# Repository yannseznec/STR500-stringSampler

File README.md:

## STR-500

This is all of the code and build info for the STR-500 gestural granular synthesizer. Watch this video for some background on the project and to see the instrument in action: https://youtu.be/luxsUPbPhyk 

The STR-500 is a granular synthesizer built for the Daisy Seed which uses a salvaged Gametrak string controller to playback a recorded sample. [Watch this video](https://youtu.be/GELGBzM0ZOE) for information on how to hack the strings out of a Gametrak. 

Here you will find a Pure Data system for running on the Daisy Seed, a KiCad project with the schematic and PCB design for the instrument, and a folder of information about the physical build including drill outlines and laser cutting files for the enclosure. Current working version is called v1.2. 

The project website can be found [here](https://www.impracticaldevices.com/docs/devices/str500/).

You can purchase a fully built STR-500, an STR-500 DIY kit, or a bare STR-500 PCB on the [Impractical Devices store on Lectronz](https://lectronz.com/stores/impracticaldevices). If they are sold out you can join the waitlist there to be notified when things are back in stock.

This project is produced by [Impractical Devices](https://www.impracticaldevices.com/), which is mainly the work of [Yann Seznec](http://www.yannseznec.com). Get in touch if you have any questions: yann@yannseznec.com.

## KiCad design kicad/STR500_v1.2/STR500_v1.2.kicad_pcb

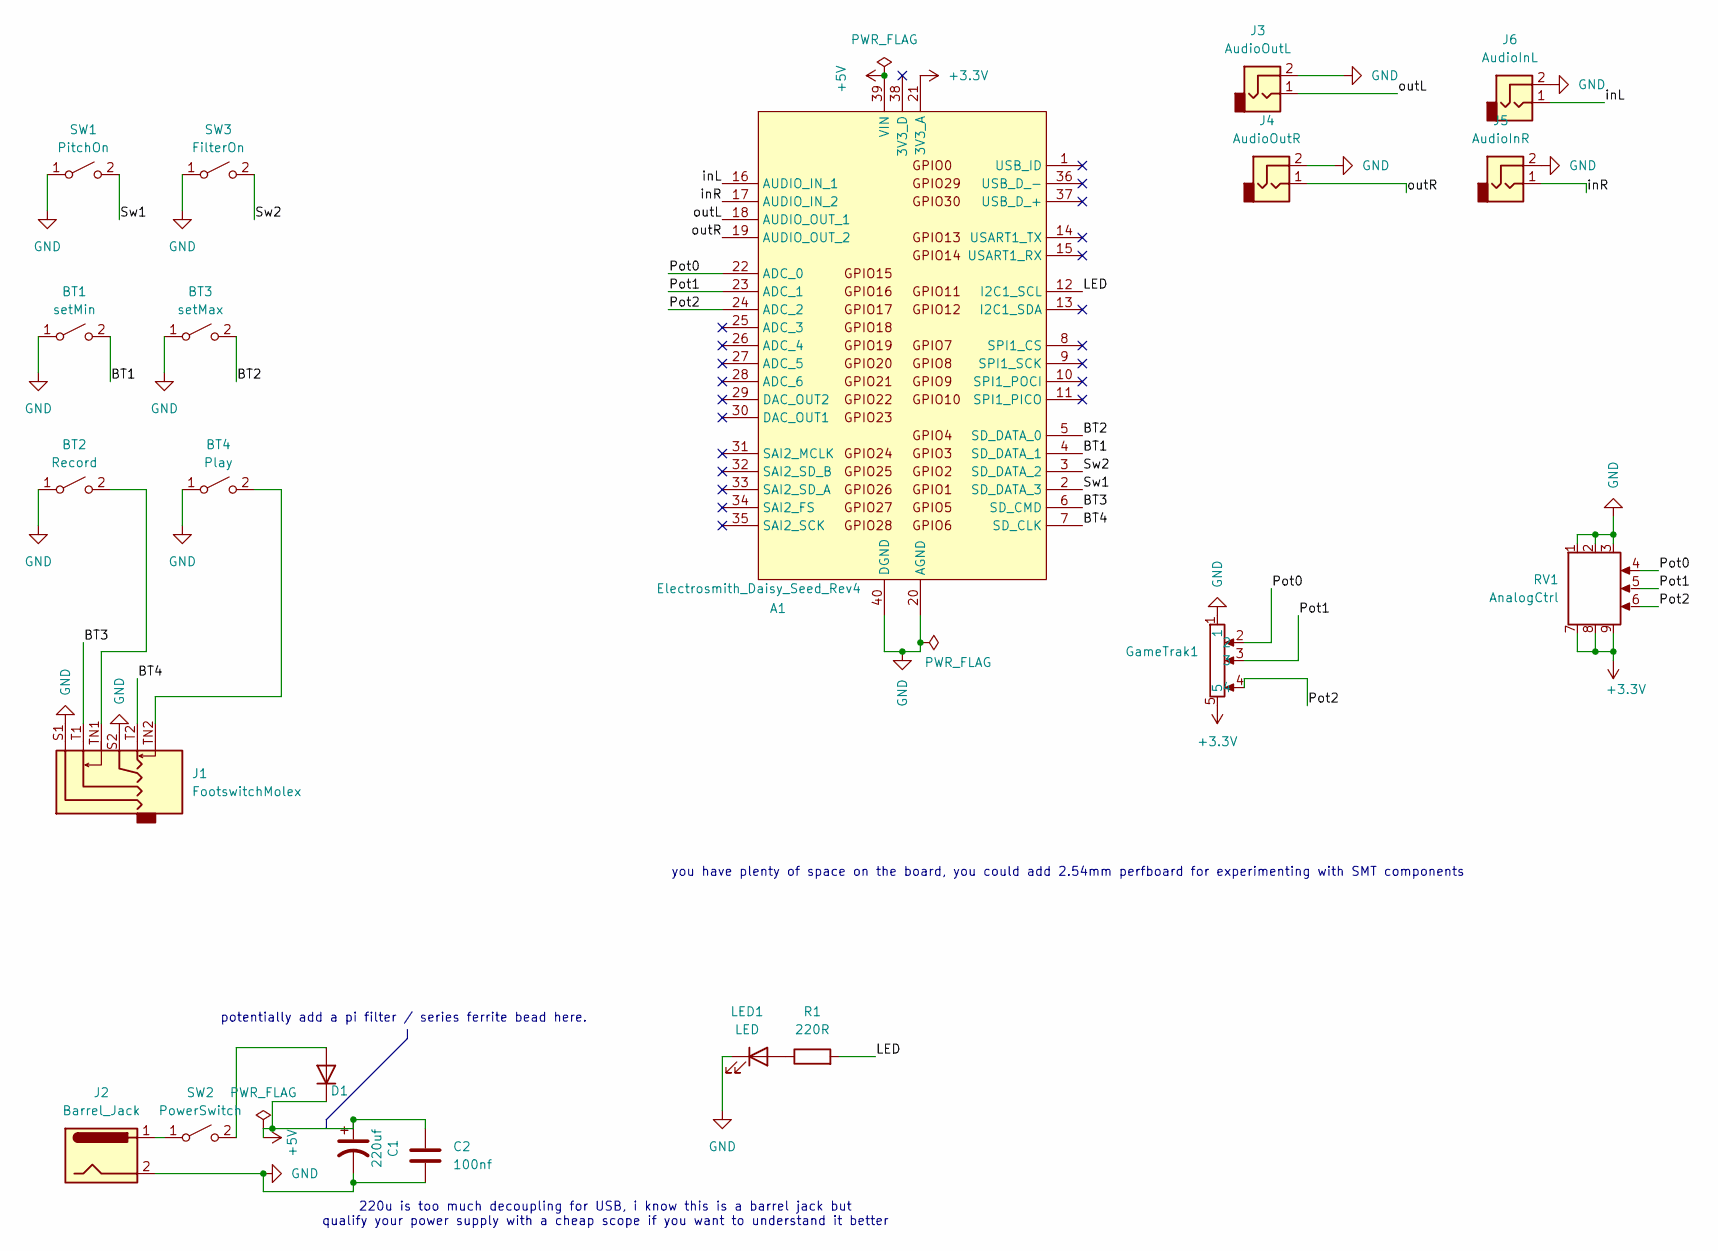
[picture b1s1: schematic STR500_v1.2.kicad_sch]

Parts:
A1: Electrosmith_Daisy_Seed_Rev4; Electrosmith_Daisy_Seed
BT1: setMin; TL1105SPF250Q
BT2: Record; SW_MEC_5GTH9
BT3: setMax; SW_PUSH_6mm
BT4: Play; SW_MEC_5GTH9
C1: 220uf; CP_Radial_D5.0mm_P2.00mm
C2: 100nf; C_Disc_D5.0mm_W2.5mm_P5.00mm
D1: D; R_Axial_DIN0207_L6.3mm_D2.5mm_P7.62mm_Horizontal
GameTrak1: Molex_Micro-Latch_53253-0570_1x05_P2.00mm_Vertical
J1: FootswitchMolex; Molex_sixpin_twoJacks
J2: Barrel_Jack; Molex_KK-254_AE-6410-02A_1x02_P2.54mm_Vertical
J3: AudioOutL; Molex_KK-254_02_pin
J4: AudioOutR; Molex_KK-254_02_pin
J5: AudioInR; Molex_KK-254_02_pin
J6: AudioInL; Molex_KK-254_02_pin
LED1: LED; LED_D5.0mm
R1: 220R; R_Axial_DIN0207_L6.3mm_D2.5mm_P7.62mm_Horizontal
RV1: AnalogCtrl; IDC-Header_2x03_P2.54mm_Vertical
SW1: PitchOn; submini_toggle
SW2: PowerSwitch; submini_toggle
SW3: FilterOn; submini_toggle

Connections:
+3.3V: A1.21 (3V3_A), GameTrak1.5, RV1.7, RV1.8, RV1.9
+5V: A1.39 (VIN), C1.1, C2.1, D1.1 (K)
/BT1: A1.4 (SD_DATA_1), BT1.2 (B)
/BT2: A1.5 (SD_DATA_0), BT3.2 (B)
/BT3: A1.6 (SD_CMD), J1.T1
/BT4: A1.7 (SD_CLK), J1.T2
/LED: A1.12 (I2C1_SCL), R1.2
/Pot0: A1.22 (ADC_0), GameTrak1.2, RV1.4
/Pot1: A1.23 (ADC_1), GameTrak1.3, RV1.5
/Pot2: A1.24 (ADC_2), GameTrak1.4, RV1.6
/Sw1: A1.2 (SD_DATA_3), SW1.2 (B)
/Sw2: A1.3 (SD_DATA_2), SW3.2 (B)
/inL: A1.16 (AUDIO_IN_1), J6.1
/inR: A1.17 (AUDIO_IN_2), J5.1
/outL: A1.18 (AUDIO_OUT_1), J3.1
/outR: A1.19 (AUDIO_OUT_2), J4.1
GND: A1.20 (AGND), A1.40 (DGND), BT1.1 (A), BT2.1 (A), BT3.1 (A), BT4.1 (A), C1.2, C2.2, GameTrak1.1, J1.S1, J1.S2, J2.2, J3.2, J4.2, J5.2, J6.2, LED1.1 (K), RV1.1, RV1.2, RV1.3, SW1.1 (A), SW3.1 (A)
unnamed: BT2.2 (B), J1.TN1
unnamed: BT4.2 (B), J1.TN2
unnamed: D1.2 (A), SW2.2 (B)
unnamed: LED1.2 (A), R1.1
unnamed: J2.1, SW2.1 (A)

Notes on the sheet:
potentially add a pi filter / series ferrite bead here.
you have plenty of space on the board, you could add 2.54mm perfboard for experimenting with SMT components
220u is too much decoupling for USB, i know this is a barrel jack but qualify your power supply with a cheap scope if you want to understand it better

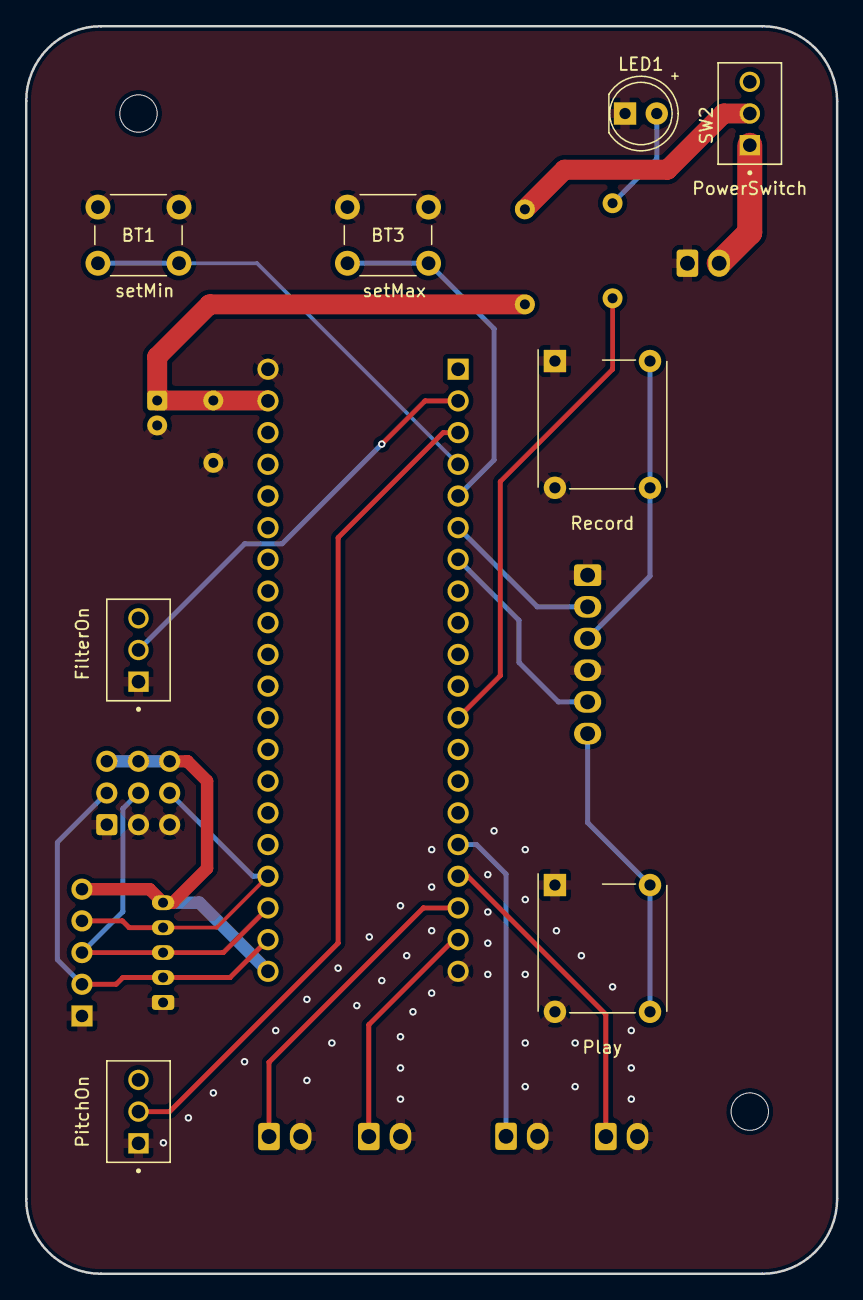
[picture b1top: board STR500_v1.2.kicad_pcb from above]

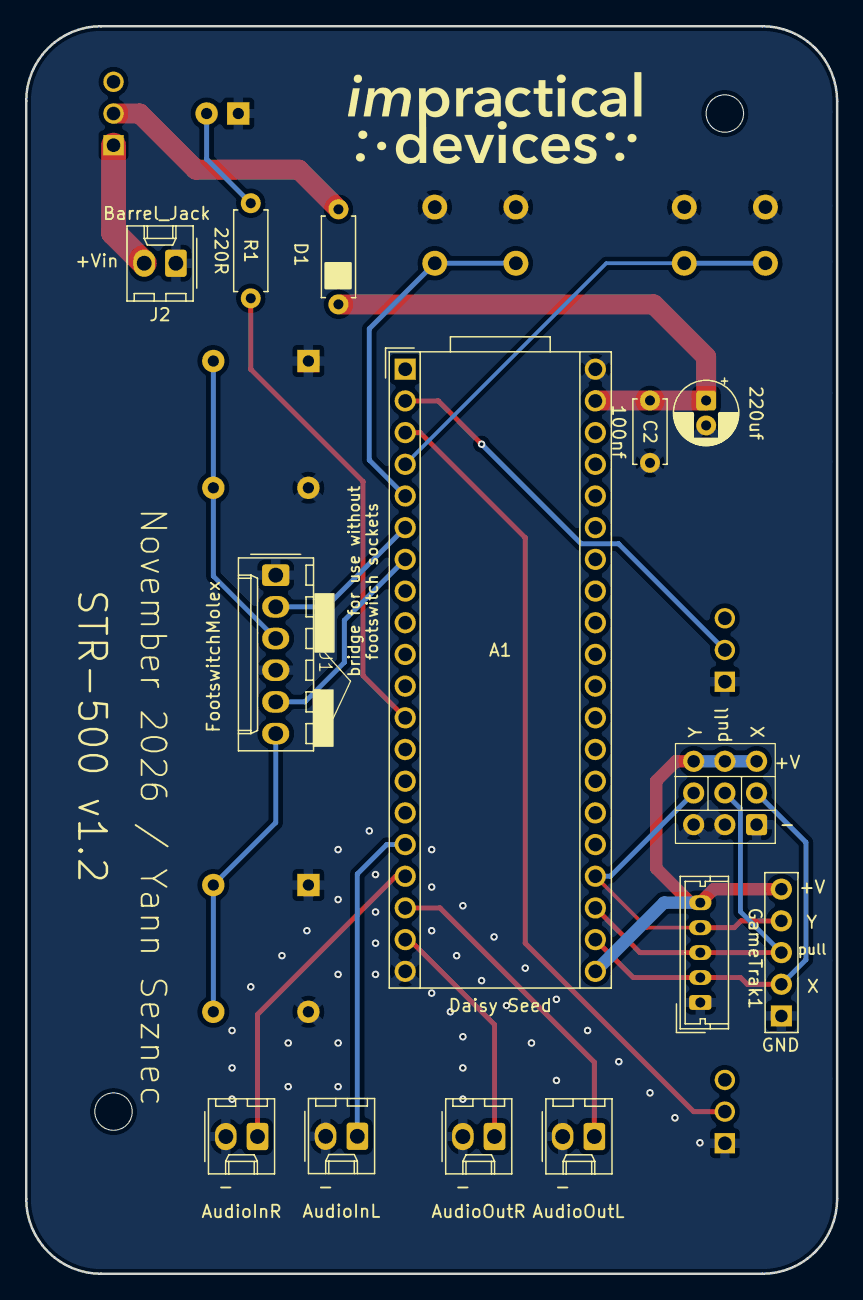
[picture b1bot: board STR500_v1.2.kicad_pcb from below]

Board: 2 copper layers, 65.0 x 100.0 mm, 21 parts (13 on the bottom side), 22 nets.

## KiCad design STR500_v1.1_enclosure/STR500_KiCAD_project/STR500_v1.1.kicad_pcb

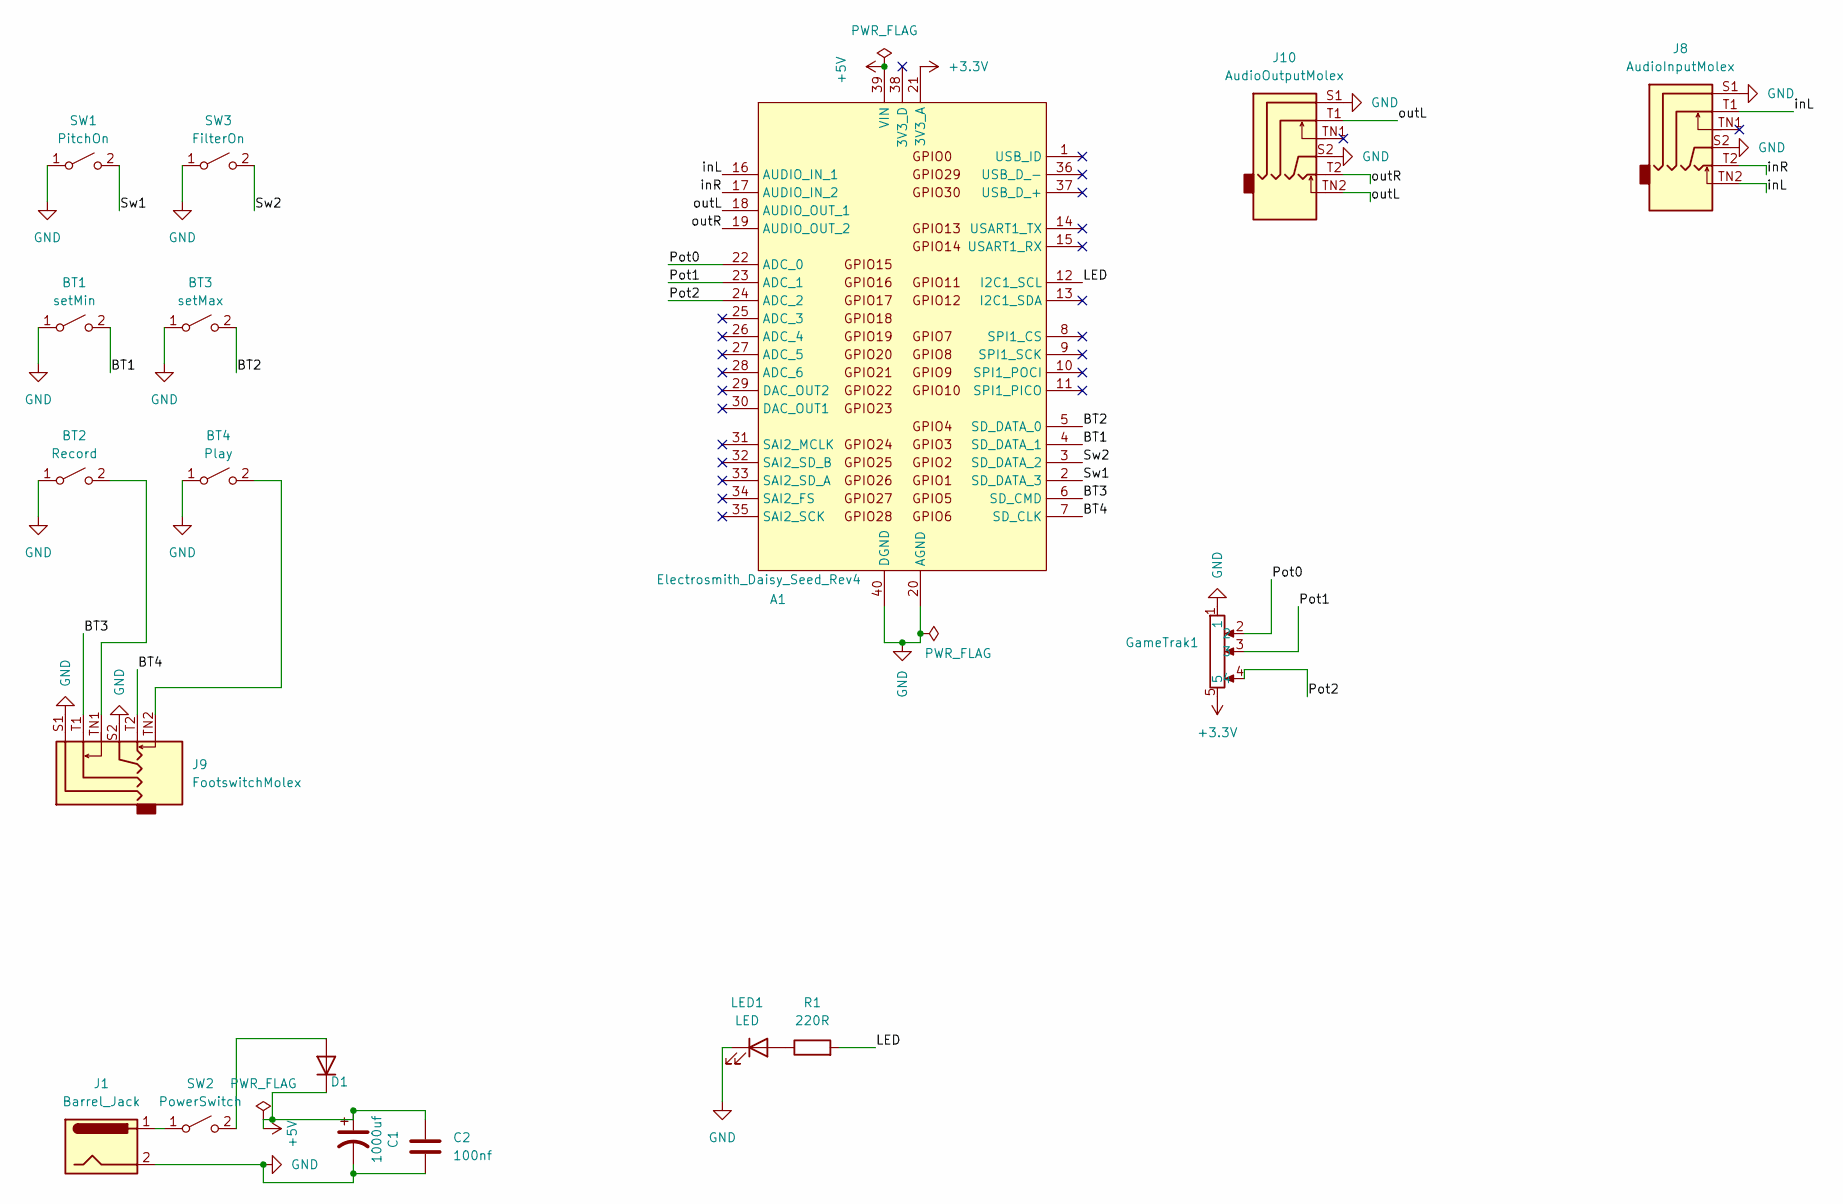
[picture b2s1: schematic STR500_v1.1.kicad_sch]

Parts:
A1: Electrosmith_Daisy_Seed_Rev4; Electrosmith_Daisy_Seed
BT1: setMin; SW_PUSH_6mm
BT2: Record; SW_TS13-1212-73-BK-160-D
BT3: setMax; SW_PUSH_6mm
BT4: Play; SW_TS13-1212-73-BK-160-D
C1: 1000uf; CP_Radial_D5.0mm_P2.00mm
C2: 100nf; C_Disc_D5.0mm_W2.5mm_P5.00mm
D1: D; R_Axial_DIN0207_L6.3mm_D2.5mm_P7.62mm_Horizontal
GameTrak1: Molex_Micro-Latch_53253-0570_1x05_P2.00mm_Vertical
J1: Barrel_Jack; Molex_KK-254_AE-6410-02A_1x02_P2.54mm_Vertical
J8: AudioInputMolex; Molex_sixpin_twoJacks
J9: FootswitchMolex; Molex_sixpin_twoJacks
J10: AudioOutputMolex; Molex_sixpin_twoJacks
LED1: LED; LED_D5.0mm
R1: 220R; R_Axial_DIN0207_L6.3mm_D2.5mm_P7.62mm_Horizontal
SW1: PitchOn; submini_toggle
SW2: PowerSwitch; submini_toggle
SW3: FilterOn; submini_toggle

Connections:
+3.3V: A1.21 (3V3_A), GameTrak1.5
+5V: A1.39 (VIN), C1.1, C2.1, D1.1 (K)
/BT1: A1.4 (SD_DATA_1), BT1.2 (B)
/BT2: A1.5 (SD_DATA_0), BT3.2 (B)
/BT3: A1.6 (SD_CMD), J9.T1
/BT4: A1.7 (SD_CLK), J9.T2
/LED: A1.12 (I2C1_SCL), R1.2
/Pot0: A1.22 (ADC_0), GameTrak1.2
/Pot1: A1.23 (ADC_1), GameTrak1.3
/Pot2: A1.24 (ADC_2), GameTrak1.4
/Sw1: A1.2 (SD_DATA_3), SW1.2 (B)
/Sw2: A1.3 (SD_DATA_2), SW3.2 (B)
/inL: A1.16 (AUDIO_IN_1), J8.T1, J8.TN2
/inR: A1.17 (AUDIO_IN_2), J8.T2
/outL: A1.18 (AUDIO_OUT_1), J10.T1, J10.TN2
/outR: A1.19 (AUDIO_OUT_2), J10.T2
GND: A1.20 (AGND), A1.40 (DGND), BT1.1 (A), BT2.1 (A), BT3.1 (A), BT4.1 (A), C1.2, C2.2, GameTrak1.1, J1.2, J8.S1, J8.S2, J9.S1, J9.S2, J10.S1, J10.S2, LED1.1 (K), SW1.1 (A), SW3.1 (A)
unnamed: BT2.2 (B), J9.TN1
unnamed: BT4.2 (B), J9.TN2
unnamed: D1.2 (A), SW2.2 (B)
unnamed: LED1.2 (A), R1.1
unnamed: J1.1, SW2.1 (A)

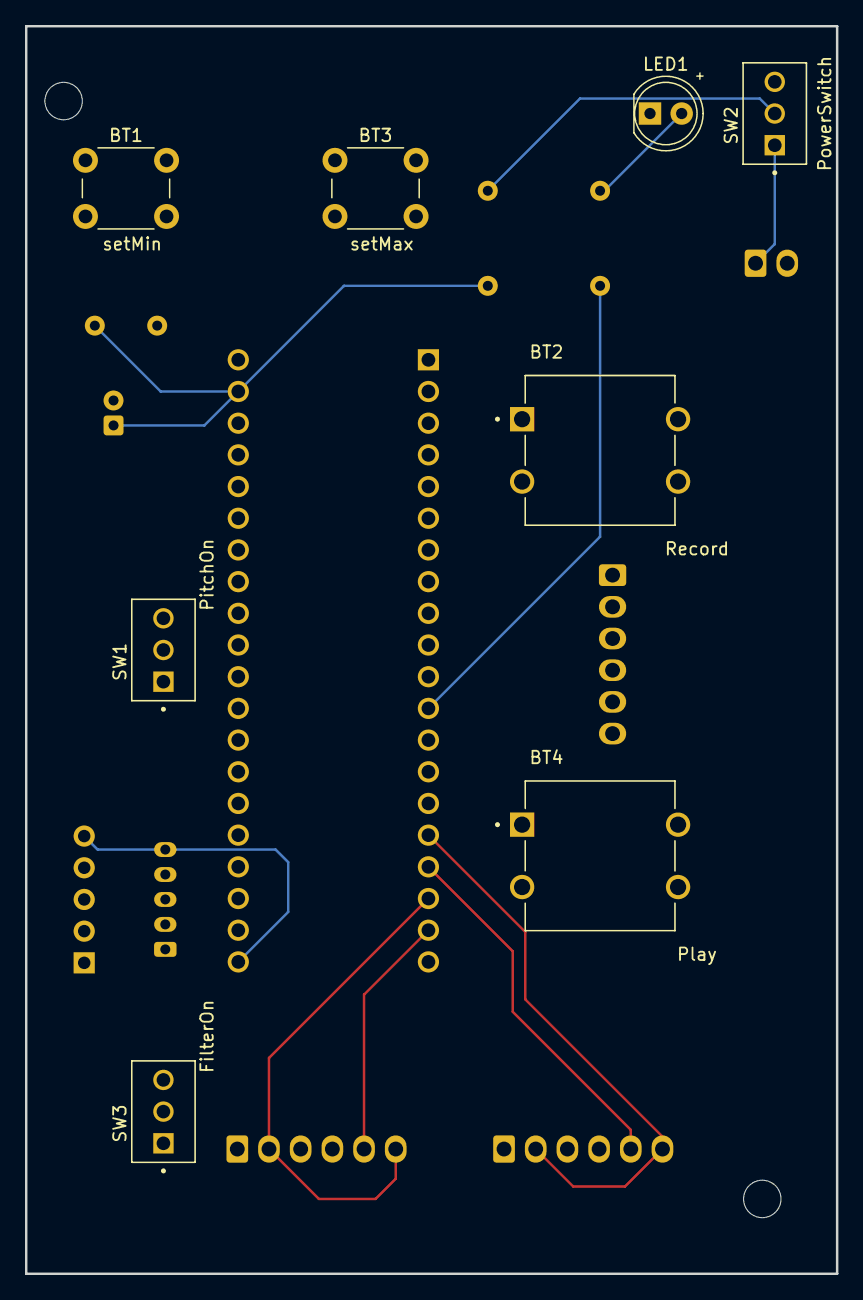
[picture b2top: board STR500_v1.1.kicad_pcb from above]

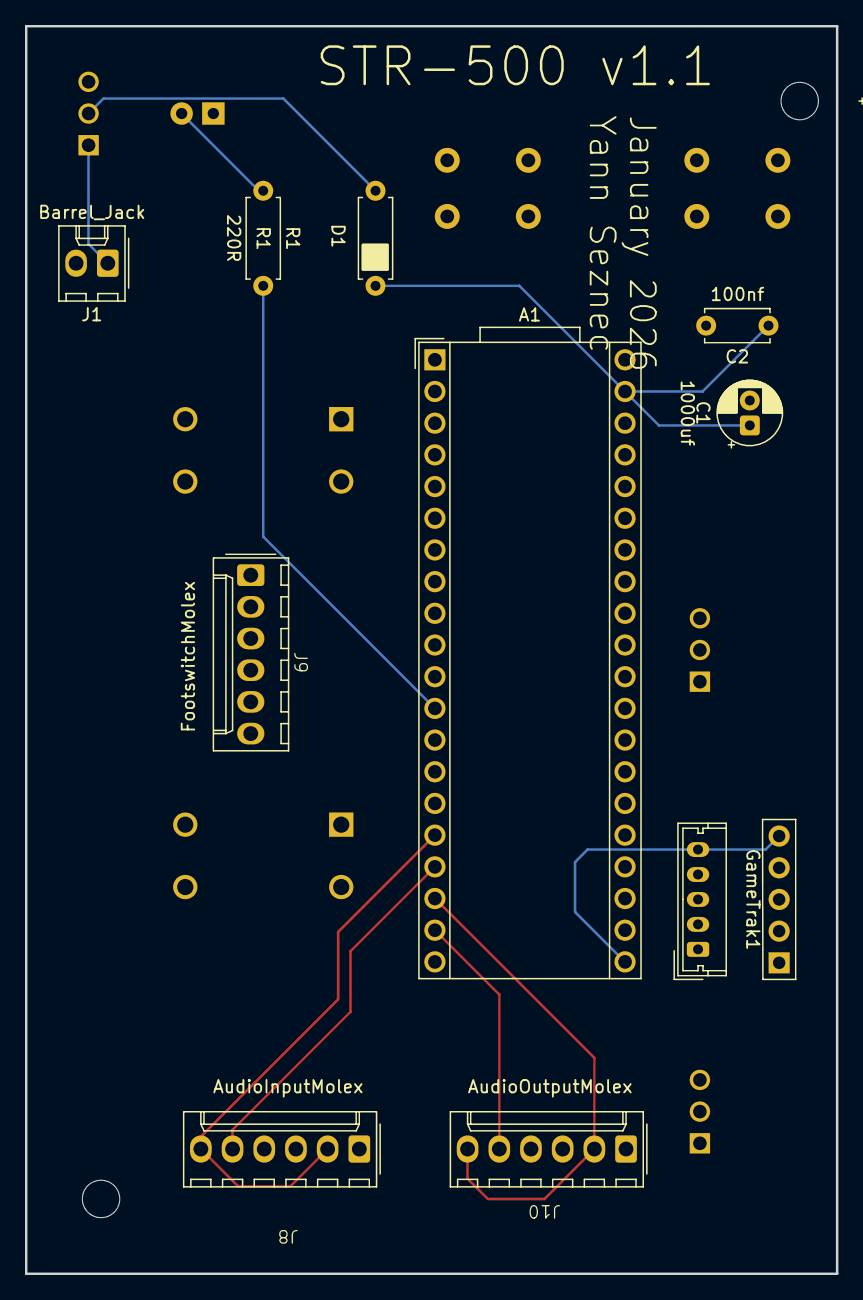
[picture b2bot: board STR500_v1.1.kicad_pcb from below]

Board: 4 copper layers, 65.0 x 100.0 mm, 18 parts (10 on the bottom side), 22 nets.

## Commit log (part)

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2025-11-06 First commit of string sampler STR-500
2025-11-06 changed the filter slightly
2026-01-21 drill files etc
2026-01-21 more drill files
2026-01-30 3d models, notes
2026-02-05 update build notes etc
2026-02-05 file reorganize
2026-02-09 more documentation
2026-02-09 Update PCB Build Notes
2026-04-12 renamed a file
